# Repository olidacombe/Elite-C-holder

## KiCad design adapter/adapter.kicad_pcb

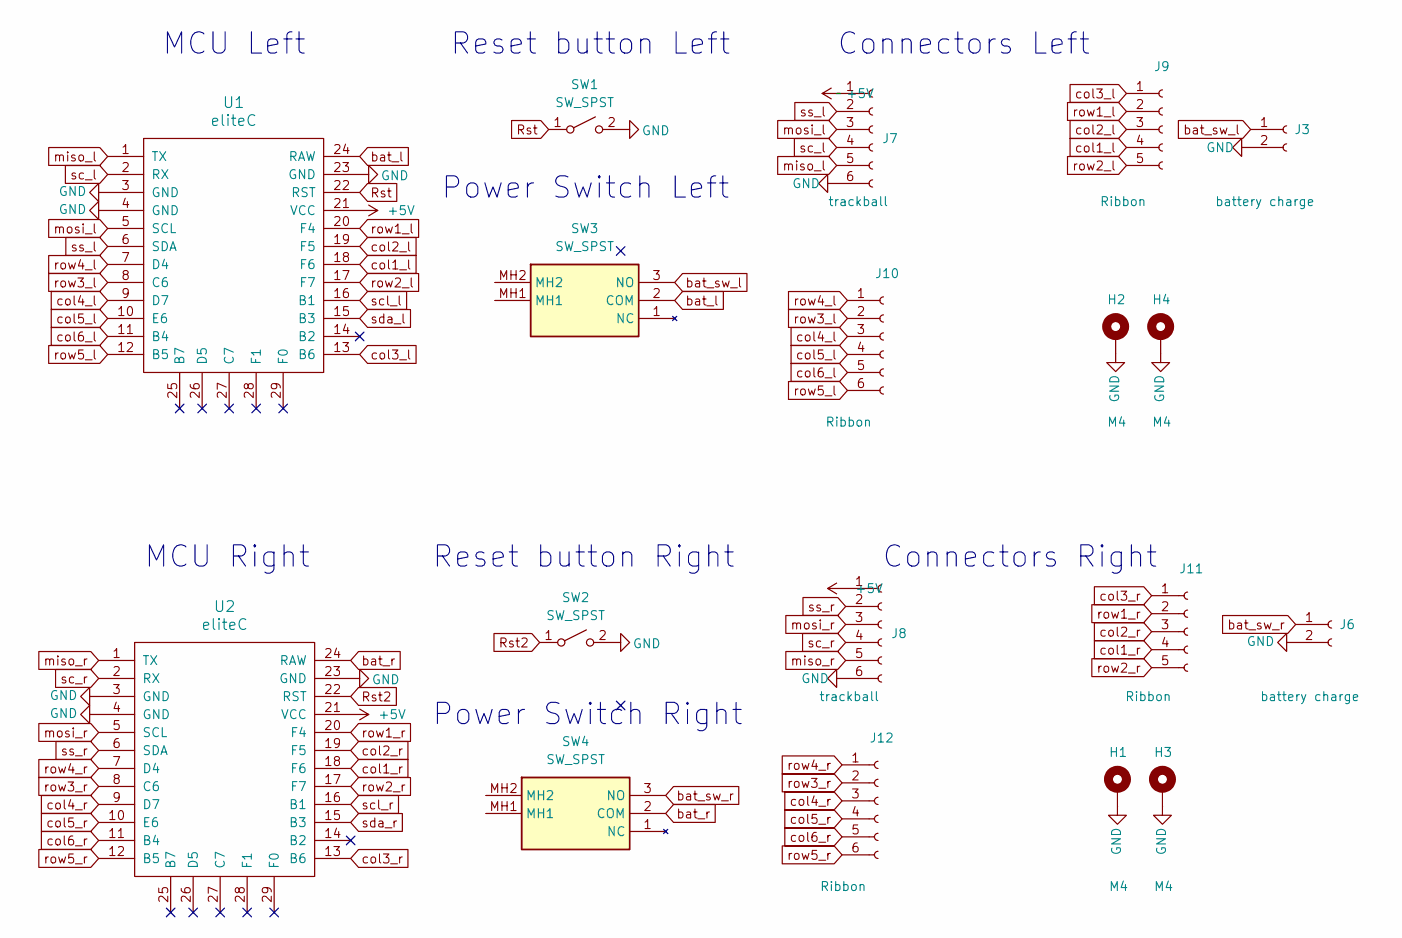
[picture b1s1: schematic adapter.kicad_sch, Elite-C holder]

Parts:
H1, H2, H3, H4: M4; MountingHole_4mm_Pad_thin
J3, J6: battery charge; JST_PH_B2B-PH-K_1x02_P2.00mm_Vertical
J7, J8: trackball; 6_PinHeader
J9, J11: Ribbon; 5_PinHeader
J10, J12: Ribbon; 6_PinHeader
SW1, SW2: SW_SPST; PushSwitch
SW3, SW4: SW_SPST; 200AWMSP2T2A1M6RE; Manufacturer_Part_Number 200AWMSP2T2A1M6RE; Mouser Part Number 612-200ASP2T2A1M6R
U1, U2: eliteC; Elite-C

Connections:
+5V: J7.1, J8.1, U1.21 (VCC), U2.21 (VCC)
GND: H1.1, H2.1, H3.1, H4.1, J3.2, J6.2, J7.6, J8.6, SW1.2 (B), SW2.2 (B), U1.3 (GND), U1.4 (GND), U1.23 (GND), U2.3 (GND), U2.4 (GND), U2.23 (GND)
Rst: SW1.1 (A), U1.22 (RST)
Rst2: SW2.1 (A), U2.22 (RST)
bat_l: SW3.2 (COM), U1.24 (RAW)
bat_r: SW4.2 (COM), U2.24 (RAW)
bat_sw_l: J3.1, SW3.3 (NO)
bat_sw_r: J6.1, SW4.3 (NO)
col1_l: J9.4, U1.18 (F6)
col1_r: J11.4, U2.18 (F6)
col2_l: J9.3, U1.19 (F5)
col2_r: J11.3, U2.19 (F5)
col3_l: J9.1, U1.13 (B6)
col3_r: J11.1, U2.13 (B6)
col4_l: J10.3, U1.9 (D7)
col4_r: J12.3, U2.9 (D7)
col5_l: J10.4, U1.10 (E6)
col5_r: J12.4, U2.10 (E6)
col6_l: J10.5, U1.11 (B4)
col6_r: J12.5, U2.11 (B4)
miso_l: J7.5, U1.1 (TX)
miso_r: J8.5, U2.1 (TX)
mosi_l: J7.3, U1.5 (SCL)
mosi_r: J8.3, U2.5 (SCL)
row1_l: J9.2, U1.20 (F4)
row1_r: J11.2, U2.20 (F4)
row2_l: J9.5, U1.17 (F7)
row2_r: J11.5, U2.17 (F7)
row3_l: J10.2, U1.8 (C6)
row3_r: J12.2, U2.8 (C6)
row4_l: J10.1, U1.7 (D4)
row4_r: J12.1, U2.7 (D4)
row5_l: J10.6, U1.12 (B5)
row5_r: J12.6, U2.12 (B5)
sc_l: J7.4, U1.2 (RX)
sc_r: J8.4, U2.2 (RX)
scl_l: U1.16 (B1)
scl_r: U2.16 (B1)
sda_l: U1.15 (B3)
sda_r: U2.15 (B3)
ss_l: J7.2, U1.6 (SDA)
ss_r: J8.2, U2.6 (SDA)

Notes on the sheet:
Power Switch Right
Reset button Left
Power Switch Left
Connectors Left
Reset button Right
MCU Left
MCU Right
Connectors Right

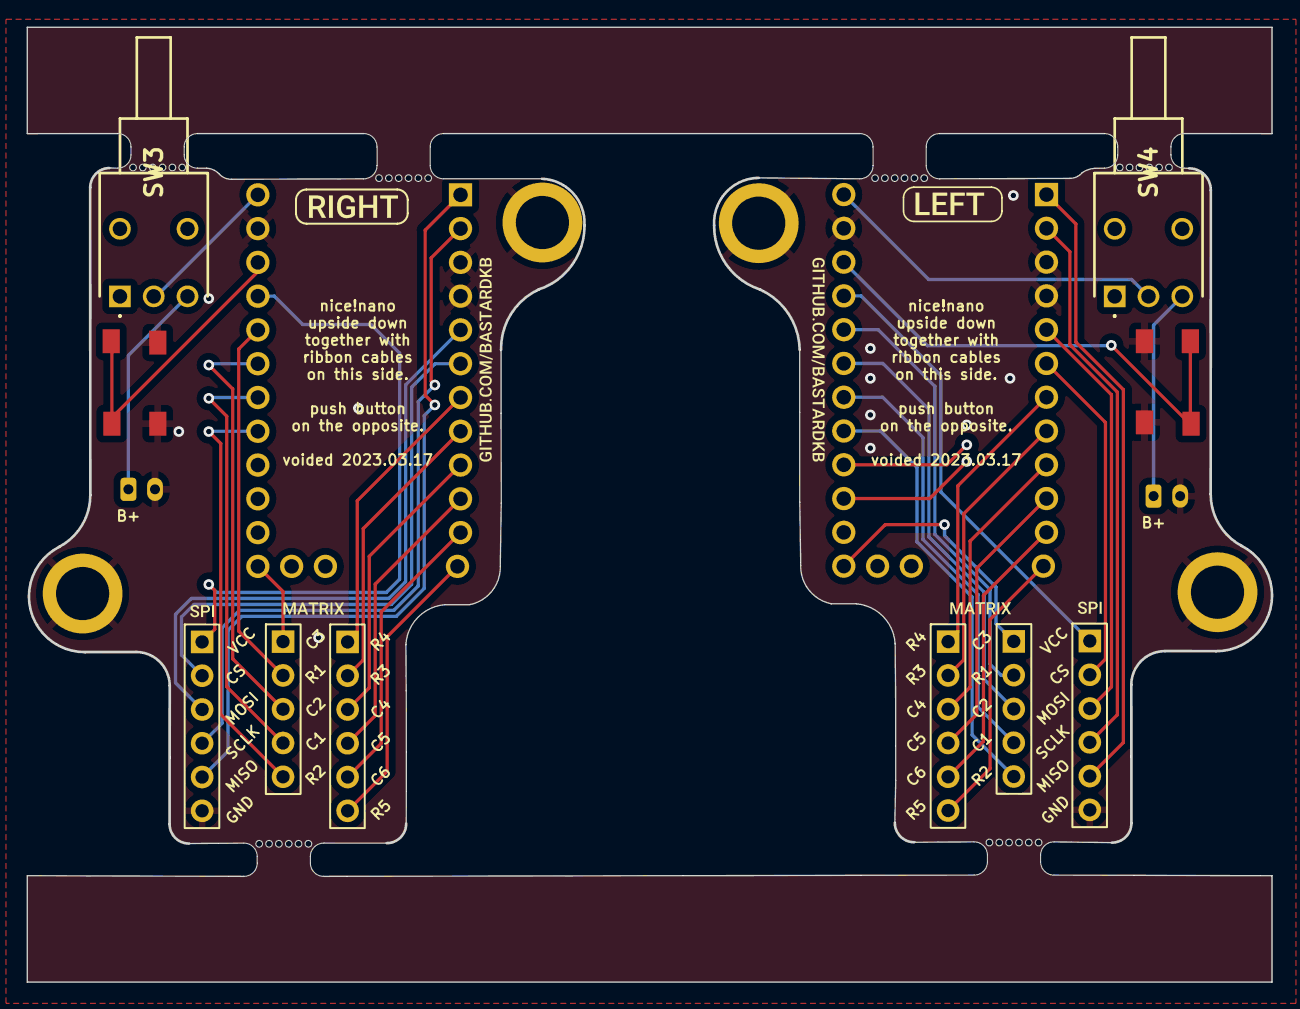
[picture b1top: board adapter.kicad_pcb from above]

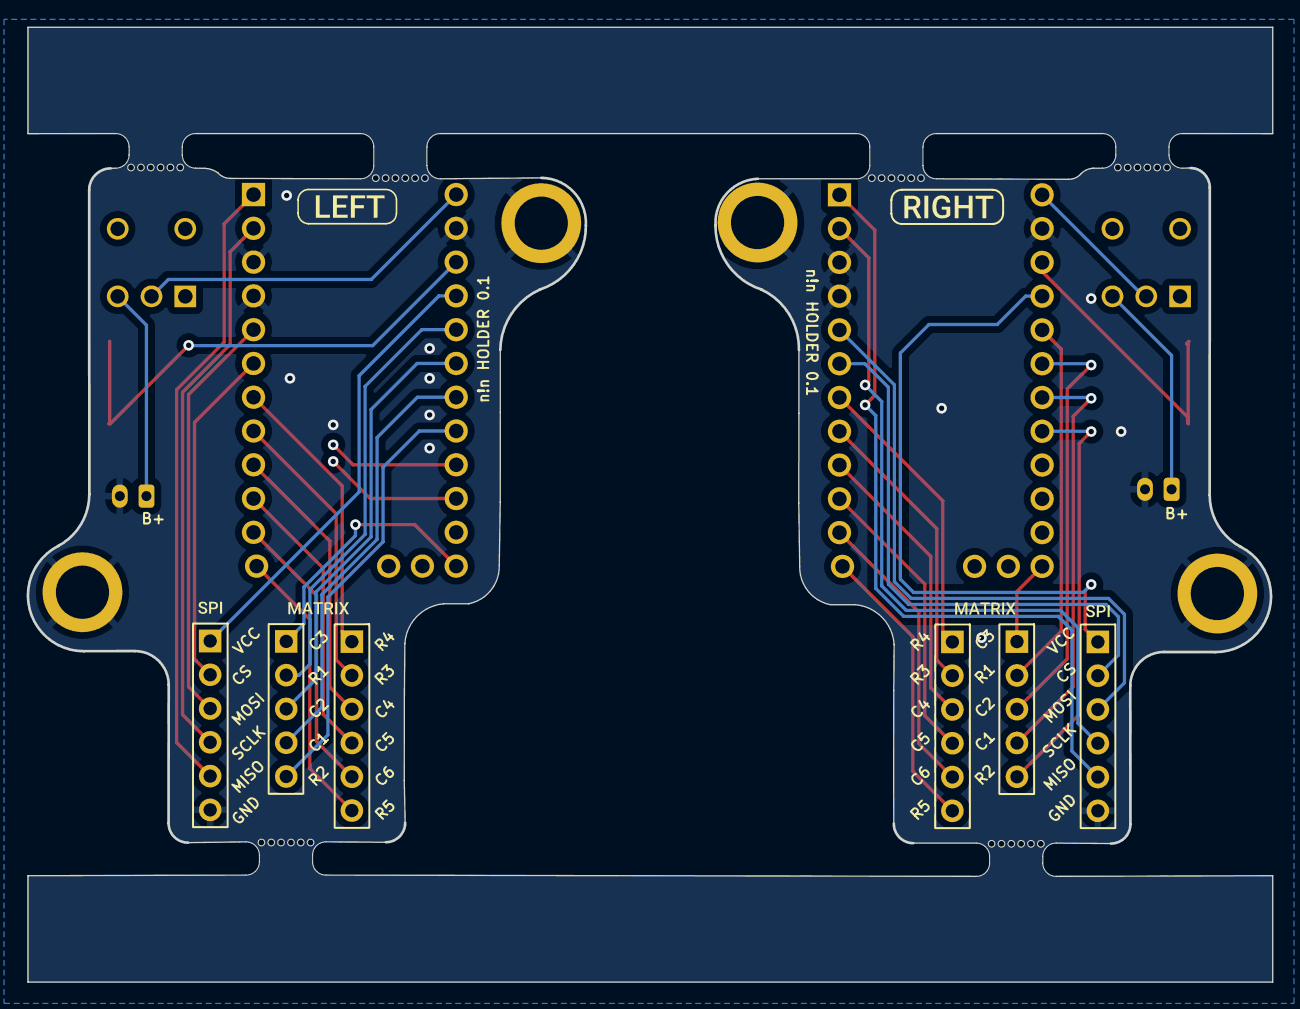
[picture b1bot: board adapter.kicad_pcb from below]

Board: 2 copper layers, 93.6 x 71.8 mm, 32 parts (8 on the bottom side), 38 nets.

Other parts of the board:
kibuzzard-61F01A92, kibuzzard-61F01A92#2: G***; kibuzzard-61F01A92
kibuzzard-61F01B61, kibuzzard-61F01B61#2: G***; kibuzzard-61F01B61
kibuzzard-61F01940, kibuzzard-61F01940#2, kibuzzard-61F01940#3, kibuzzard-61F01940#4: G***; kibuzzard-61F01940
kibuzzard-61F01957, kibuzzard-61F01957#2, kibuzzard-61F01957#3, kibuzzard-61F01957#4: G***; kibuzzard-61F01957
kibuzzard-6208EFFE, kibuzzard-6208EFFE#2: G***; kibuzzard-6208EFFE

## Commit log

2023-09-23 remove fill and unused serial connectors
2023-09-23 mark mousebites not in schematic
2023-09-23 simplify
2023-09-23 tailor
2023-09-24 update keeping holes
2023-09-24 place
2023-09-24 route
2023-09-24 rendered
2023-11-05 avoid confusion by cleaning up original gerbers (some on discord seem interested in printing this)

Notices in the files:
adapter/adapter.kicad_sch:
Licensed under CERN-OHL-W v2
